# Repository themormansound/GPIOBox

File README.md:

# GPIOBox
GPIO relay box, 8 channel.

We needed some relays to trigger things. I made one card with each 8 relays. You can add whichever D2N style relay you like.

Jim

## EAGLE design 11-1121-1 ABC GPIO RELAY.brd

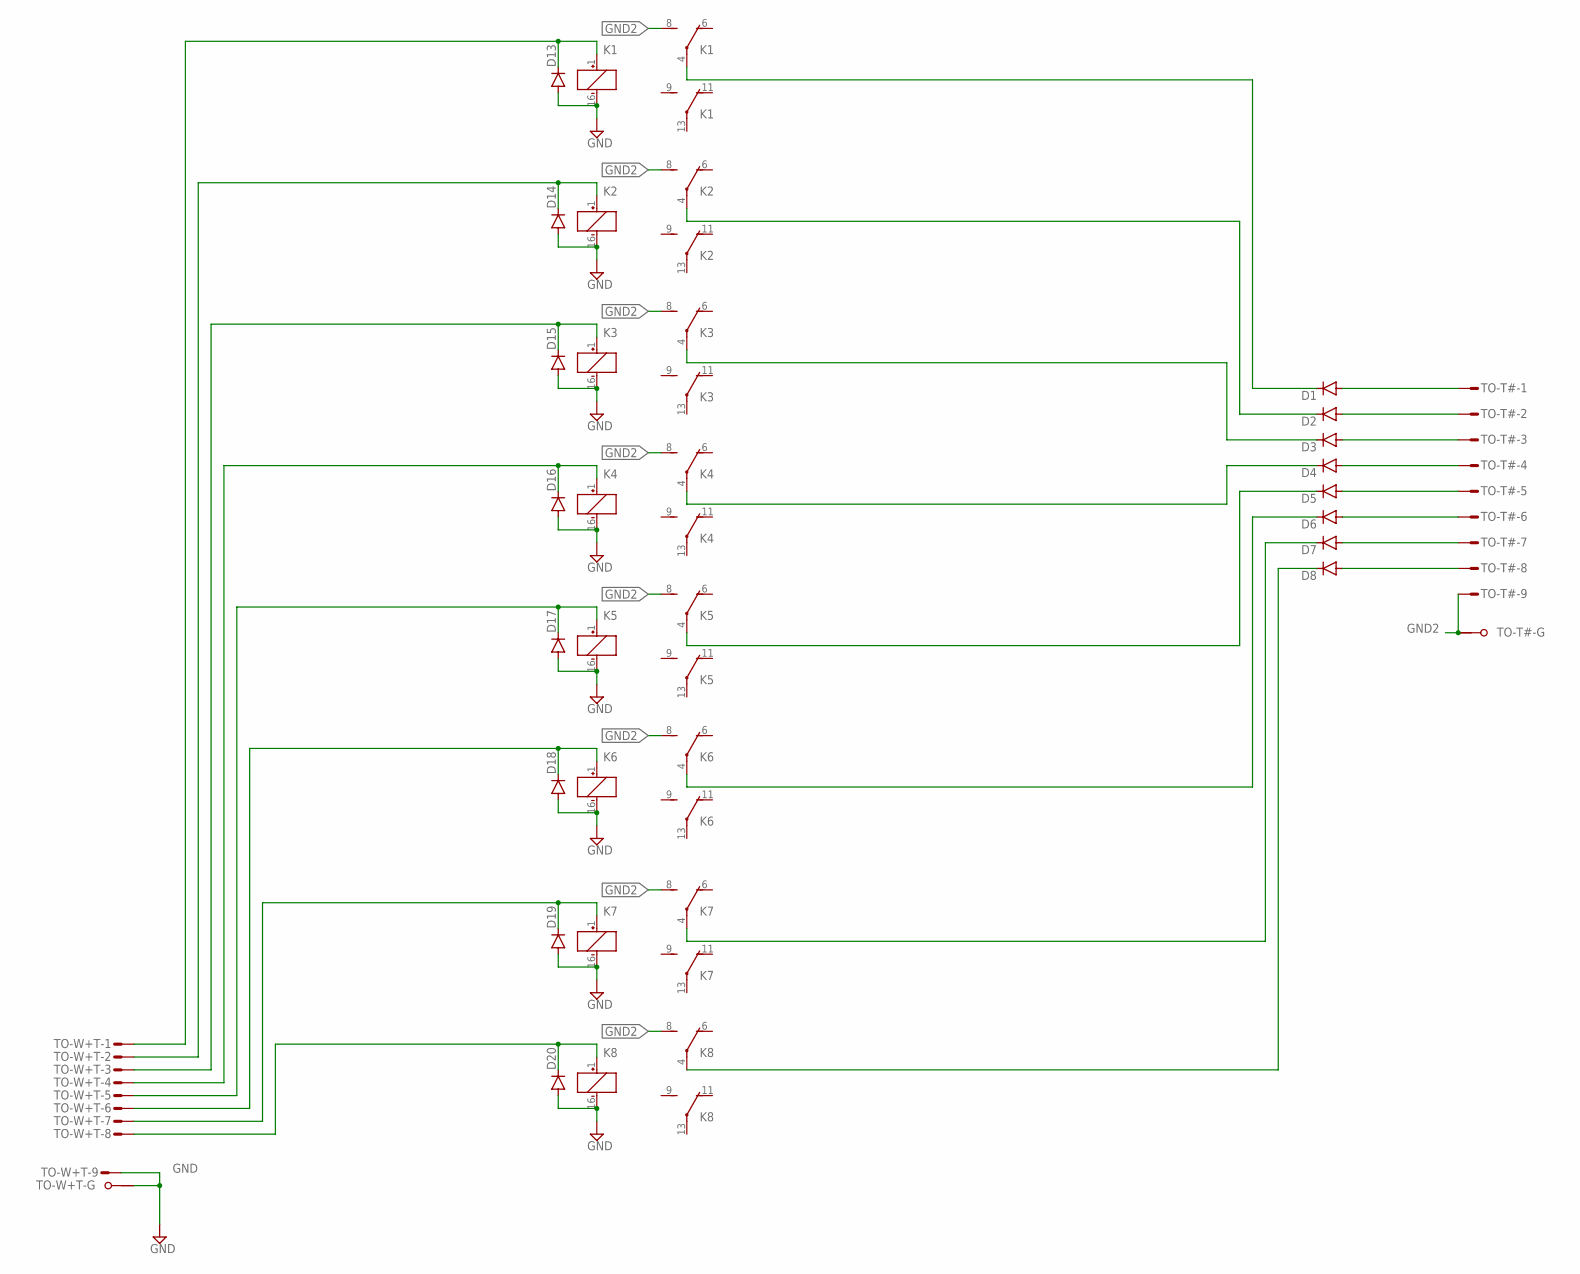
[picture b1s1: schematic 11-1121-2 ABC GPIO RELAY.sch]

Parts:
D1, D2, D3, D4, D5, D6, D7, D8, D13, D14, D15, D16, D17, D18, D19, D20: DIODE-DO214AA; DO214AA
K1, K2, K3, K4, K5, K6, K7, K8: DS2Y-S-DC12V; DS2Y
TO-T#: M09HPS; M09HP
TO-W+T: M09HPS; M09HP

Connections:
GND: D13.A, D14.A, D15.A, D16.A, D17.A, D18.A, D19.A, D20.A, K1.16 (-), K2.16 (-), K3.16 (-), K4.16 (-), K5.16 (-), K6.16 (-), K7.16 (-), K8.16 (-), TO-W+T.9 (M), TO-W+T.G1
GND2: K1.8 (S), K2.8 (S), K3.8 (S), K4.8 (S), K5.8 (S), K6.8 (S), K7.8 (S), K8.8 (S), TO-T#.9 (M), TO-T#.G1
unnamed: D13.C, K1.1 (+), TO-W+T.1 (M)
unnamed: D1.A, TO-T#.1 (M)
unnamed: D2.A, TO-T#.2 (M)
unnamed: D3.A, TO-T#.3 (M)
unnamed: D4.A, TO-T#.4 (M)
unnamed: D5.A, TO-T#.5 (M)
unnamed: D6.A, TO-T#.6 (M)
unnamed: D7.A, TO-T#.7 (M)
unnamed: D8.A, TO-T#.8 (M)
unnamed: D14.C, K2.1 (+), TO-W+T.2 (M)
unnamed: D15.C, K3.1 (+), TO-W+T.3 (M)
unnamed: D16.C, K4.1 (+), TO-W+T.4 (M)
unnamed: D17.C, K5.1 (+), TO-W+T.5 (M)
unnamed: D18.C, K6.1 (+), TO-W+T.6 (M)
unnamed: D19.C, K7.1 (+), TO-W+T.7 (M)
unnamed: D20.C, K8.1 (+), TO-W+T.8 (M)
unnamed: D1.C, K1.4
unnamed: D2.C, K2.4
unnamed: D3.C, K3.4
unnamed: D4.C, K4.4
unnamed: D5.C, K5.4
unnamed: D6.C, K6.4
unnamed: D7.C, K7.4
unnamed: D8.C, K8.4

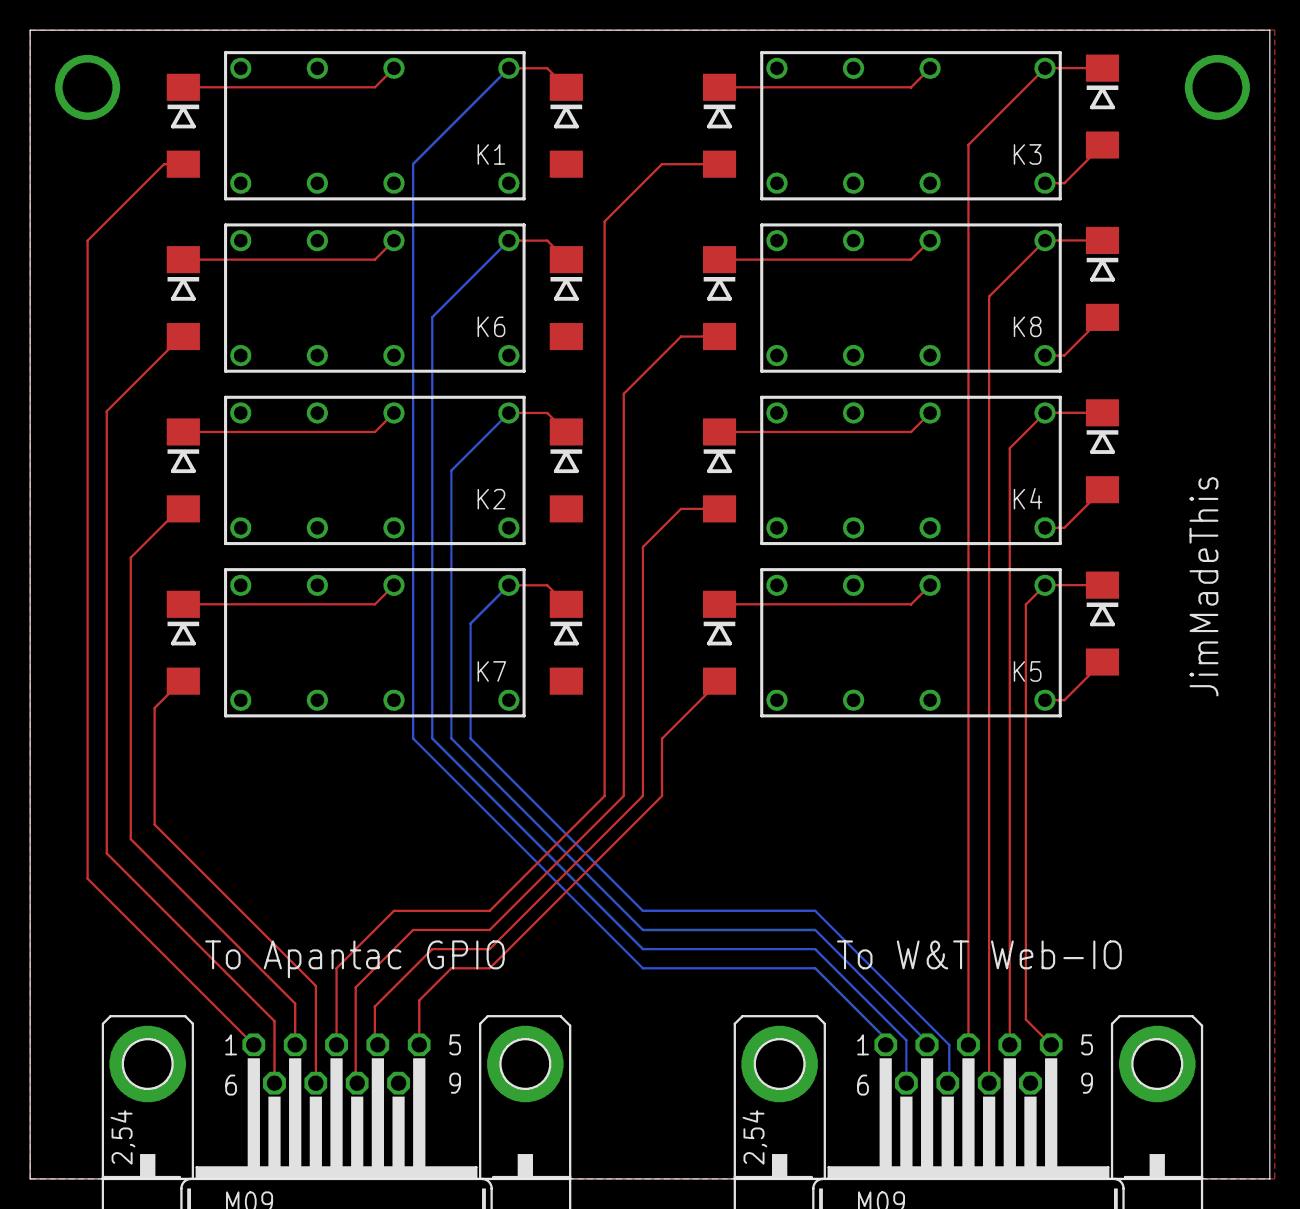
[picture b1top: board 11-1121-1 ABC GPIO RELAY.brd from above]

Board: 2 copper layers, 82.2 x 76.2 mm, 26 parts (0 on the bottom side), 26 nets.
